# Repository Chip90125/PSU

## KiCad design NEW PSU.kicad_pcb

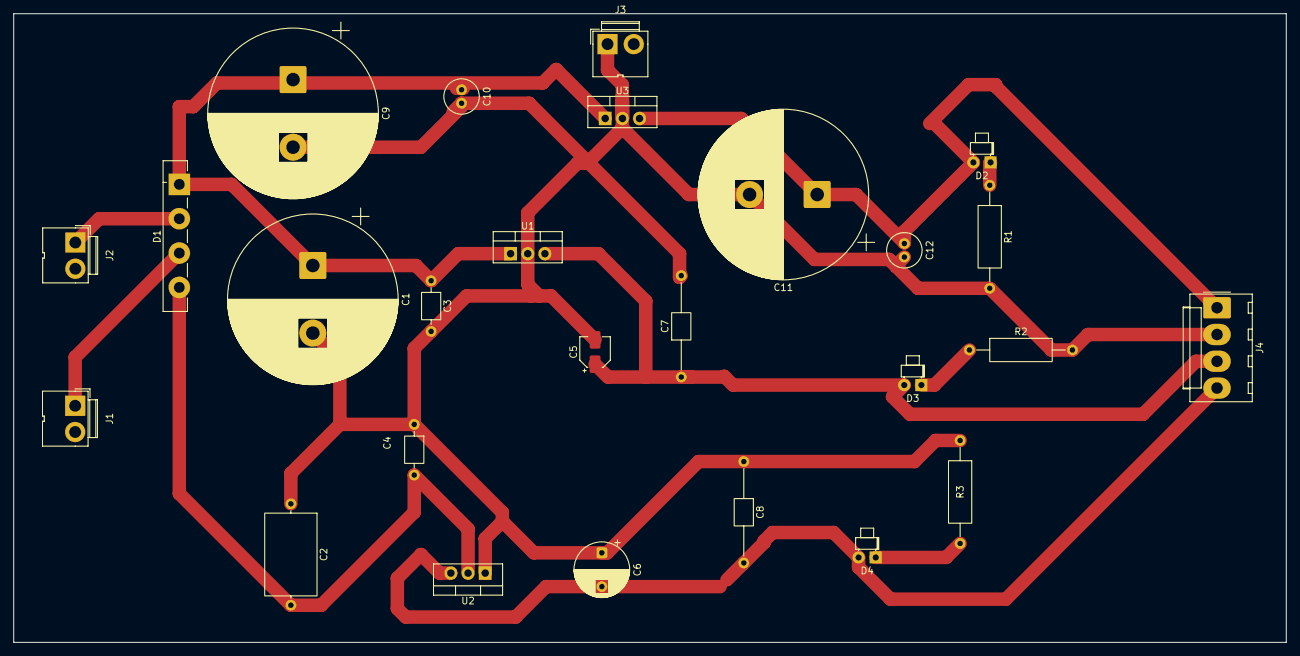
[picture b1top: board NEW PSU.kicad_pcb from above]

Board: 2 copper layers, 188.2 x 93.0 mm, 26 parts (0 on the bottom side), 11 nets.

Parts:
C1: 2200uF\35v; CP_Radial_D25.0mm_P10.00mm_SnapIn
C2: 2200uf\50v; C_Axial_L12.0mm_D7.5mm_P15.00mm_Horizontal
C3: 100nF\25v; C_Axial_L3.8mm_D2.6mm_P7.50mm_Horizontal
C4: 100nf\25v; C_Axial_L3.8mm_D2.6mm_P7.50mm_Horizontal
C5: 10uF\25v; CP_Elec_4x3
C6: 10uF\25v; CP_Radial_D8.0mm_P5.00mm
C7: 1uF; C_Axial_L3.8mm_D2.6mm_P15.00mm_Horizontal
C8: 1uf; C_Axial_L3.8mm_D2.6mm_P15.00mm_Horizontal
C9: 100uF\35v; CP_Radial_D25.0mm_P10.00mm_SnapIn
C10: 10uF\25v; C_Radial_D5.0mm_H11.0mm_P2.00mm
C11: 10uF\25v; CP_Radial_D25.0mm_P10.00mm_SnapIn
C12: 1uF\25v; C_Radial_D5.0mm_H11.0mm_P2.00mm
D1: GBU8A; Diode_Bridge_Vishay_GBU
D2, D3, D4: LED; LED_D1.8mm_W1.8mm_H2.4mm_Horizontal_O1.27mm_Z1.6mm
J1, J2, J3: Conn_01x01_Socket; JWT_A3963_1x02_P3.96mm_Vertical
J4: Conn_01x04; Molex_KK-396_A-41791-0004_1x04_P3.96mm_Vertical
R1, R2, R3: 2000; R_Axial_DIN0309_L9.0mm_D3.2mm_P15.24mm_Horizontal
U1: L7812; TO-220-3_Vertical
U2: L7912; TO-220-3_Vertical
U3: L7805; TO-220-3_Vertical

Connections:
GND: C1.2, C2.1, C3.2, C4.1, C5.2, C6.1, C7.2, C8.1, C9.2, C10.2, C11.2, C12.2, J3.1, J4.2, R1.2, R2.2, R3.1, U1.2 (GND), U2.1 (GND), U3.2 (GND)
unnamed: C1.1, C3.1, C9.1, C10.1, D1.1 (+), U1.1 (IN), U3.1 (IN)
unnamed: C2.2, C4.2, D1.4 (-), U2.2 (VI)
unnamed: C11.1, C12.1, D2.2 (A), J4.1, U3.3 (OUT)
unnamed: D2.1 (K), R1.1
unnamed: C5.1, C7.1, D3.2 (A), J4.3, U1.3 (OUT)
unnamed: D3.1 (K), R2.1
unnamed: C6.2, C8.2, D4.2 (A), J4.4, U2.3 (VO)
unnamed: D4.1 (K), R3.2
unnamed: D1.3, J1.1
unnamed: D1.2, J2.1
